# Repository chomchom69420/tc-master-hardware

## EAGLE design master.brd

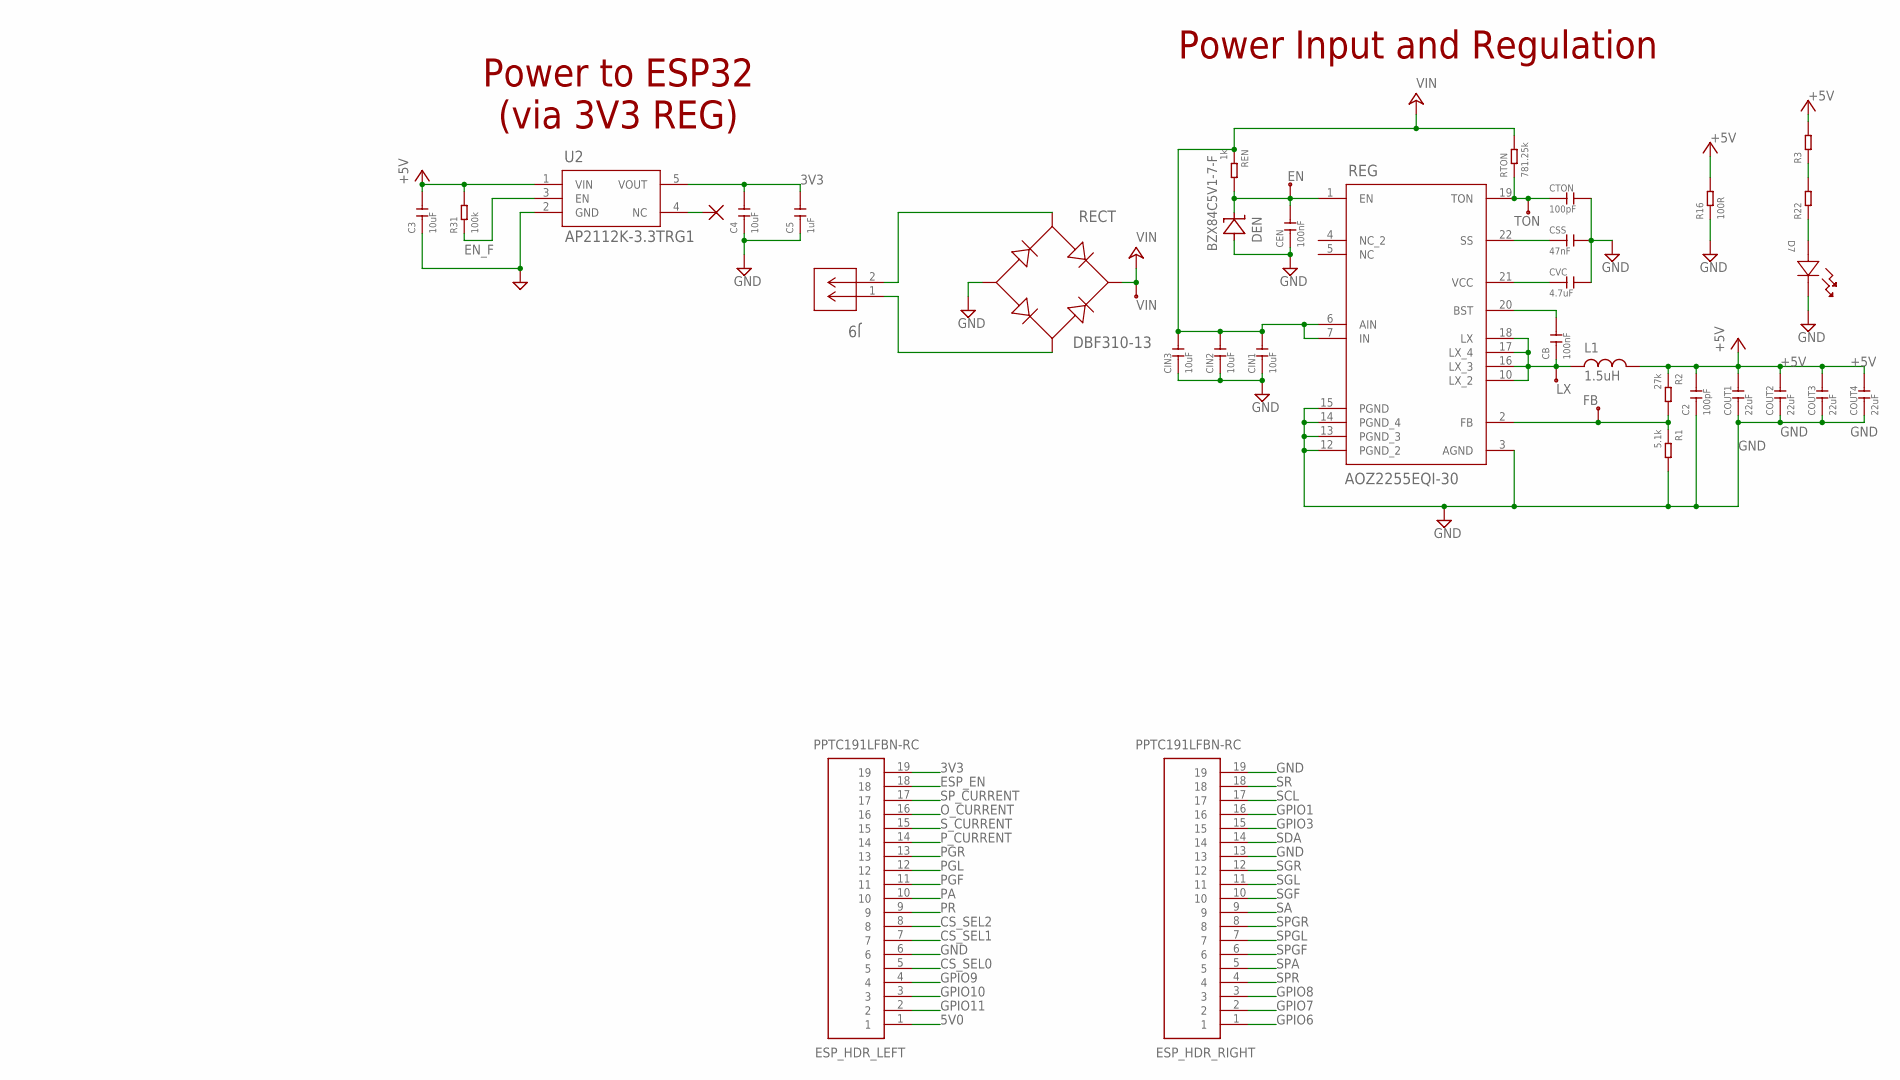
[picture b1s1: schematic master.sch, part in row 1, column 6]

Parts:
C2: 100pF; C0603
C3, C4: 10uF; C0805
C5: 1uF; C0603
CB: 100nF; C0603
CEN: 100nF; C0603
CIN1, CIN2, CIN3: 10uF; C0805
COUT1, COUT2, COUT3, COUT4: 22uF; C1206
CSS: 47nF; C0603
CTON: 100pF; C0402
CVC: 4.7uF; C0402
D7: VLMY1500-GS08; LED_1500-GS08_VIS
DEN: BZX84C5V1-7-F; SOT23
EN: CONN_HDR_1POS_0.1; 1X1
ESP_HDR_LEFT: PPTC191LFBN-RC; RHDR19W80P0X254_1X19_4876X254X
ESP_HDR_RIGHT: PPTC191LFBN-RC; RHDR19W80P0X254_1X19_4876X254X
FB: CONN_HDR_1POS_0.1; 1X1
J9: 1715250000; CONN2_250000_WED
L1: 1.5uH; BCIH1367-2R2M
LX: CONN_HDR_1POS_0.1; 1X1
R1: 5.1k; R0603
R2: 27k; R0603
R3: 1k; R0402
R16: 100R; PR-D2.7XL8.5MM
R22: 0R; R0402
R31: 100k; R0402
RECT: DBF310-13; DBF_DIO
REG: AOZ2255EQI-30; QFN_4X4_22L-EP2_S_AOS
REN: 1k; R0603
RTON: 781.25k; R0603
TON: CONN_HDR_1POS_0.1; 1X1
U2: AP2112K-3.3TRG1; SOT_RG1_DIO
VIN: CONN_HDR_1POS_0.1; 1X1

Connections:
3V3: C4.2, C5.2, ESP_HDR_LEFT.19, U2.5 (VOUT)
5V0: ESP_HDR_LEFT.1
+5V: C2.2, C3.2, COUT1.2, COUT2.2, COUT3.2, COUT4.2, L1.P$2 (2), R2.1, R3.2, R16.2, R31.2, U2.1 (VIN)
+12V: J9.2, RECT.2
BST: CB.2, REG.20 (BST)
CS_SEL0: ESP_HDR_LEFT.5
CS_SEL1: ESP_HDR_LEFT.7
CS_SEL2: ESP_HDR_LEFT.8
EN: CEN.2, DEN.P$3 (C), EN.1, REG.1 (EN), REN.2
EN_F: R31.1, U2.3 (EN)
ESP_EN: ESP_HDR_LEFT.18
FB: FB.1, R1.1, R2.2, REG.2 (FB)
GND: C2.1, C3.1, C4.1, C5.1, CEN.1, CIN1.1, CIN2.1, CIN3.1, COUT1.1, COUT2.1, COUT3.1, COUT4.1, CSS.2, CTON.2, CVC.2, D7.1, DEN.P$1 (A), ESP_HDR_LEFT.6, ESP_HDR_RIGHT.13, ESP_HDR_RIGHT.19, R1.2, R16.1, RECT.3, REG.3 (AGND), REG.12 (PGND_2), REG.13 (PGND_3), REG.14 (PGND_4), REG.15 (PGND), U2.2 (GND)
GPIO1: ESP_HDR_RIGHT.16
GPIO3: ESP_HDR_RIGHT.15
GPIO6: ESP_HDR_RIGHT.1
GPIO7: ESP_HDR_RIGHT.2
GPIO8: ESP_HDR_RIGHT.3
GPIO9: ESP_HDR_LEFT.4
GPIO10: ESP_HDR_LEFT.3
GPIO11: ESP_HDR_LEFT.2
LX: CB.1, L1.P$1 (1), LX.1, REG.10 (LX_2), REG.16 (LX_3), REG.17 (LX_4), REG.18 (LX)
unnamed: R3.1, R22.2
unnamed: D7.2, R22.1
unnamed: J9.1, RECT.4
O_CURRENT: ESP_HDR_LEFT.16
PA: ESP_HDR_LEFT.10
PGF: ESP_HDR_LEFT.11
PGL: ESP_HDR_LEFT.12
PGR: ESP_HDR_LEFT.13
PR: ESP_HDR_LEFT.9
P_CURRENT: ESP_HDR_LEFT.14
SA: ESP_HDR_RIGHT.9
SCL: ESP_HDR_RIGHT.17
SDA: ESP_HDR_RIGHT.14
SGF: ESP_HDR_RIGHT.10
SGL: ESP_HDR_RIGHT.11
SGR: ESP_HDR_RIGHT.12
SPA: ESP_HDR_RIGHT.5
SPGF: ESP_HDR_RIGHT.6
SPGL: ESP_HDR_RIGHT.7
SPGR: ESP_HDR_RIGHT.8
SPR: ESP_HDR_RIGHT.4
SP_CURRENT: ESP_HDR_LEFT.17
SR: ESP_HDR_RIGHT.18
SS: CSS.1, REG.22 (SS)
S_CURRENT: ESP_HDR_LEFT.15
TON: CTON.1, REG.19 (TON), RTON.1, TON.1
VCC: CVC.1, REG.21 (VCC)
VIN: CIN1.2, CIN2.2, CIN3.2, RECT.1, REG.6 (AIN), REG.7 (IN), REN.1, RTON.2, VIN.1

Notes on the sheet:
Power Input and Regulation
Power to ESP32 (via 3V3 REG)

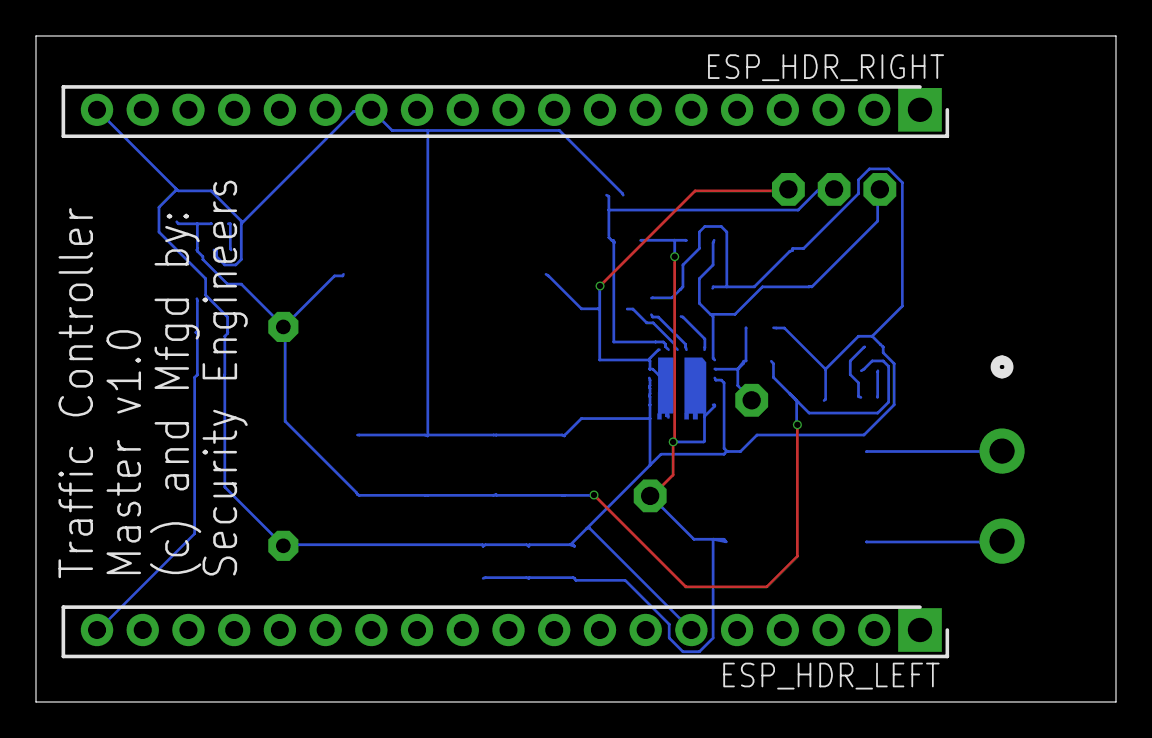
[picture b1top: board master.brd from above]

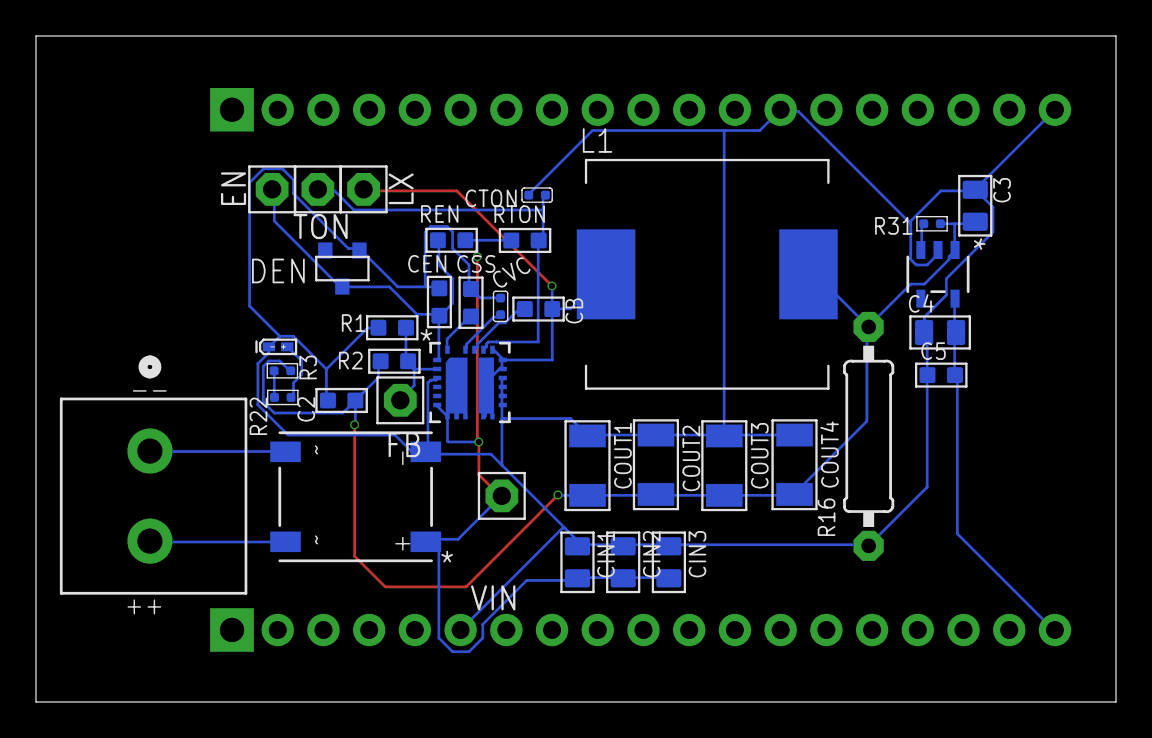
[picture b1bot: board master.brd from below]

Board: 2 copper layers, 60.0 x 37.0 mm, 38 parts (36 on the bottom side), 16 nets.

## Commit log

2023-08-10 init commit
2023-08-24 init commit : finalized schematic and board
2023-08-24 temp commit no change
2023-08-29 added jlc cpl and bom files, added gerber files zip

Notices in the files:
parts and their libraries:
COPYRIGHT: Copyright (C) 2022 Ultra Librarian. All rights reserved.
COPYRIGHT: Copyright (C) 2023 Ultra Librarian. All rights reserved.
